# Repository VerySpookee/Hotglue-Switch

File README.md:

# Overview
This PCB project is a power switch PCB for use in 2S Antweight combat robots.

Power is enabled by fastening an M1.6 screw against the PCB surface.
An additional M2 sized hole is provided for mounting.

# Changelog:
## V1.0:
 - First batch of PCBs built and tested.
 - Black PCB with white silkscreen.
 - M3 mounting hole.

## V1.1:
 - Reduced overall PCB size and reduced clearance between components.
 - Replaced Wurth Elektronik SMD standoff with Sinhoo SMD standoff.
 - Downsized M3 mounting hole to M2.
 - Changed current limiting resistor for less blinding LED and downsized to 0603 package.
 - Added fillet to corners of PCB because I can.

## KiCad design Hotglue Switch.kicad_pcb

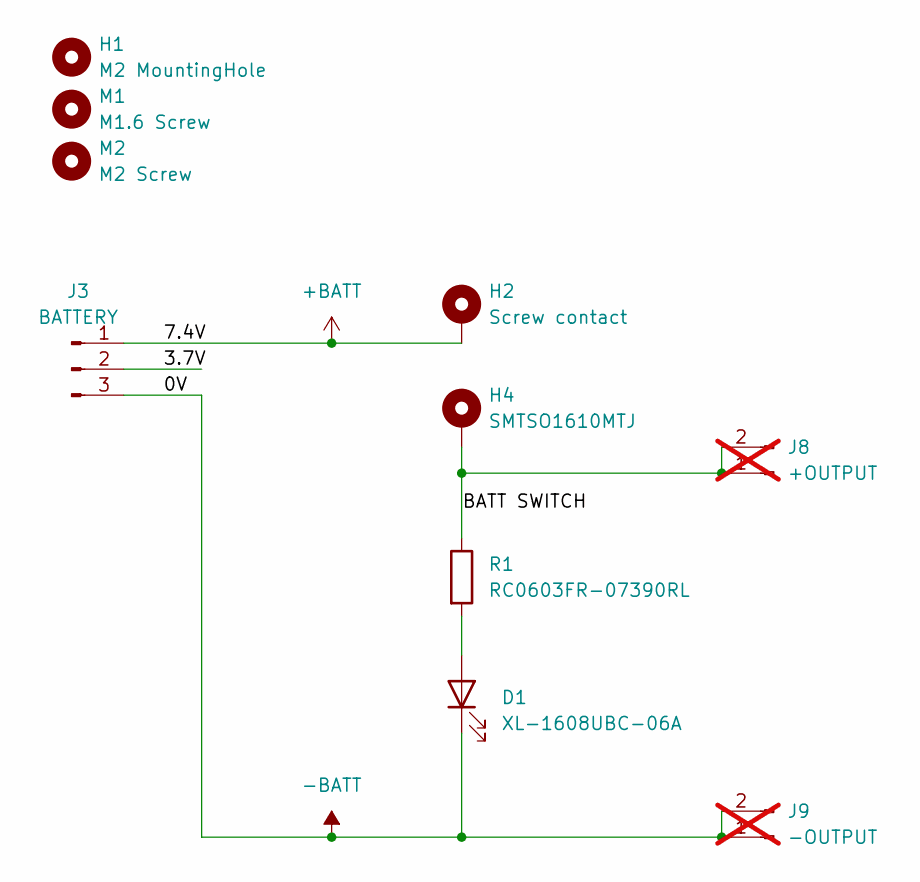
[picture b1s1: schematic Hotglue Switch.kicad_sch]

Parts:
D1: XL-1608UBC-06A; LED_0603_1608Metric_Pad1.05x0.95mm_HandSolder
H1: M2 MountingHole; MountingHole_2.2mm_M2_DIN965
H2: Screw contact; Sinhoo-M1.6-screw-contact
H4: SMTSO1610MTJ; Mounting_Sinhoo_SMTSO1610MJT
J3: BATTERY; JST_XH_S3B-XH-A-1_1x03_P2.50mm_Horizontal_Aliexpress
J8: +OUTPUT; PinHeader_1x02_P2.54mm_Vertical Positive; not fitted
J9: -OUTPUT; PinHeader_1x02_P2.54mm_Vertical Negative; not fitted
M1: M1.6 Screw; Screw M1.6
M2: M2 Screw; Screw M2
R1: RC0603FR-07390RL; R_0603_1608Metric_Pad0.98x0.95mm_HandSolder

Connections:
+BATT: H2.1, J3.1
-BATT: D1.1 (K), J3.3, J9.1, J9.2
/3.7V: J3.2
/BATT SWITCH: H4.1, J8.1, J8.2, R1.1
unnamed: D1.2 (A), R1.2

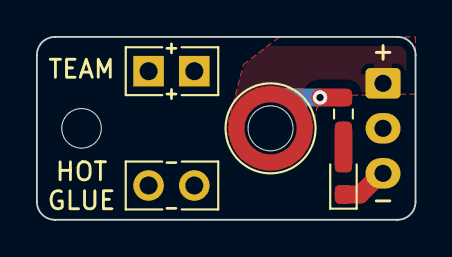
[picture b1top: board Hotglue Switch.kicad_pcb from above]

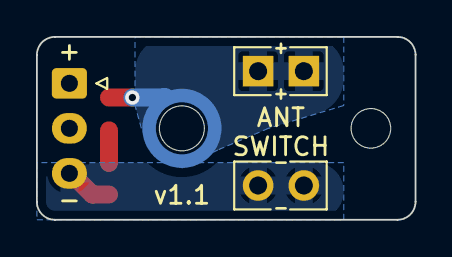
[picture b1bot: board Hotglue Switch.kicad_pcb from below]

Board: 2 copper layers, 21.0 x 10.2 mm, 10 parts (2 on the bottom side), 4 nets.

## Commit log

2025-02-20 Update Hotglue Switch.kicad_pcb
    fixed pcb thickness to 0.8mm for standoff clearance.
    Replaced routed tracks with polygon pours
2025-02-20 generate gerbers and panel
    generated gerbers and drill files for single pcb.
    generated 5x2 panel
    generated gerbers and drill files for panel
2025-02-21 updated outputs for pcbway and jlc specific panels
2025-02-22 added 3d models
2025-11-17 commit of all modified files for rev 1.1, including gerbers, 3d step models, PCB, schematic, and project files.
2025-11-17 update readme to add changelog
2025-11-17 Deleted gerber folders and project associated with the panelised outputs. Turns out it's a pain in the bum to generate a panel that corresponds to the rules and preferences of each fab house, much ea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
